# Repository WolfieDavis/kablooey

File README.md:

# kablooey

arduino based jumbo i spy game with visual interface using processing

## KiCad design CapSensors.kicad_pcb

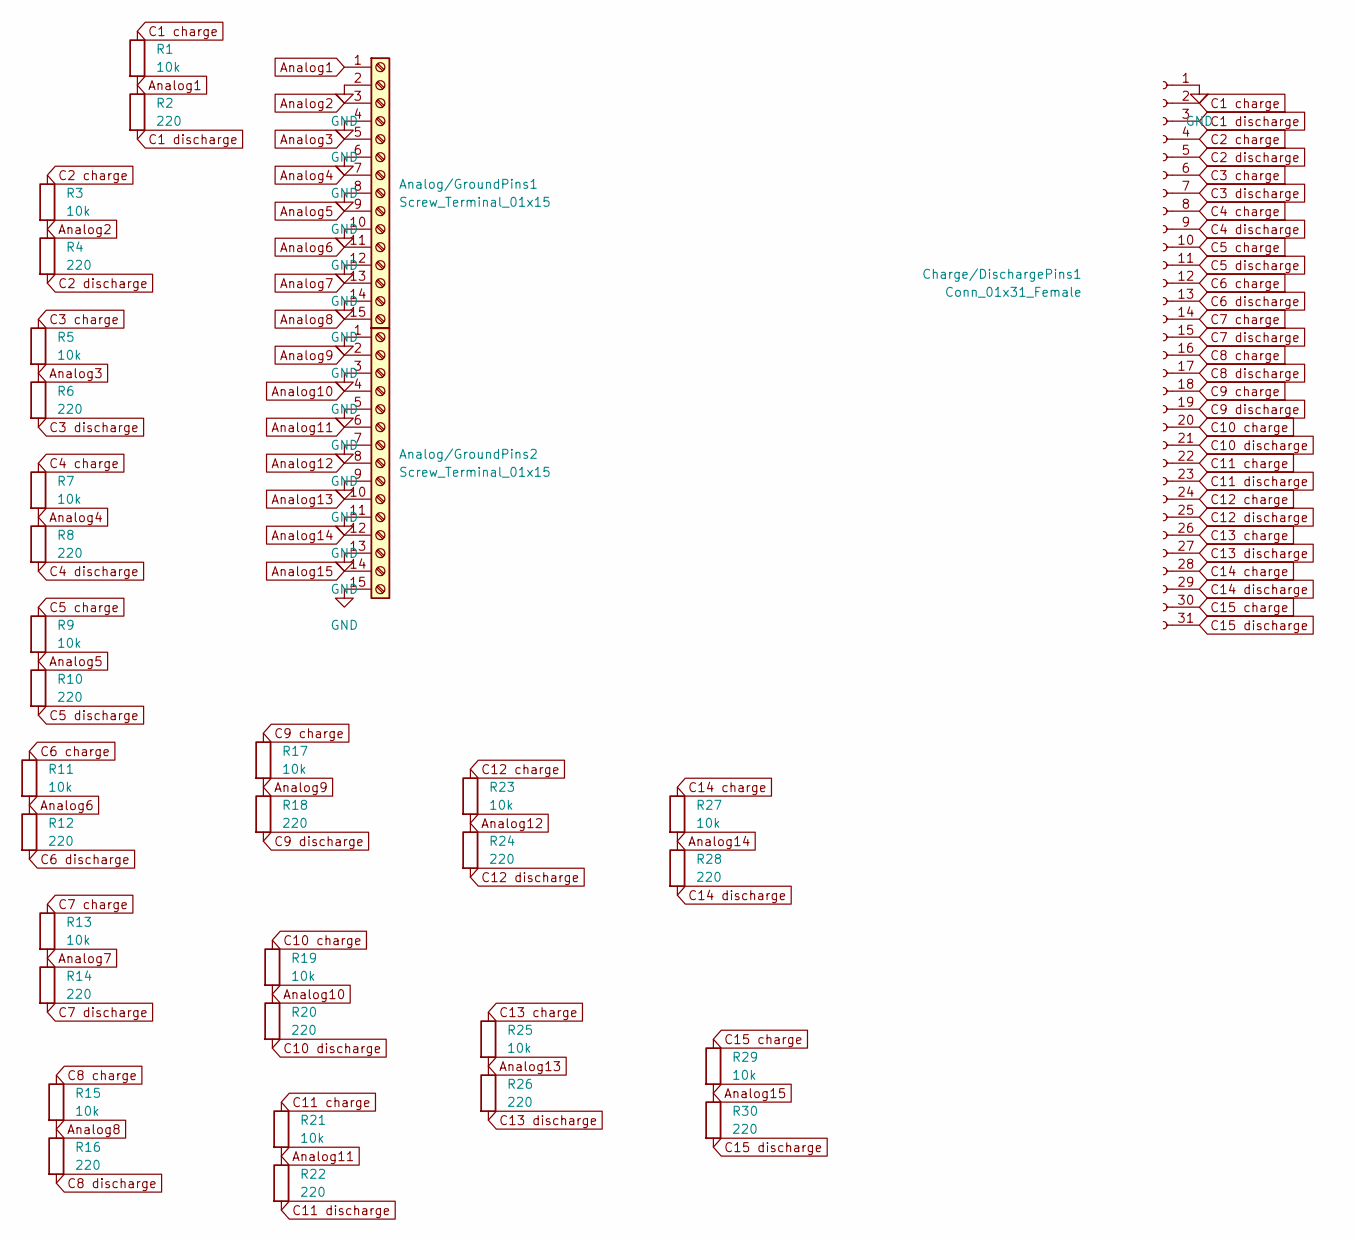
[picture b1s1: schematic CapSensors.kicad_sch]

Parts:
Analog/GroundPins1, Analog/GroundPins2: Screw_Terminal_01x15; PinHeader_1x15_P2.54mm_Vertical
Charge/DischargePins1: Conn_01x31_Female; PinHeader_1x31_P2.54mm_Vertical
R1, R3, R5, R7, R9, R11, R13, R15, R17, R19, R21, R23, R25, R27, R29: 10k; R_0603_1608Metric
R2, R4, R6, R8, R10, R12, R14, R16, R18, R20, R22, R24, R26, R28, R30: 220; R_0603_1608Metric

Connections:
Analog1: Analog/GroundPins1.1, R1.2, R2.1; also elsewhere on the board
Analog2: Analog/GroundPins1.3, R3.2, R4.1; also elsewhere on the board
Analog3: Analog/GroundPins1.5, R5.2, R6.1; also elsewhere on the board
Analog4: Analog/GroundPins1.7, R7.2, R8.1; also elsewhere on the board
Analog5: Analog/GroundPins1.9, R9.2, R10.1; also elsewhere on the board
Analog6: Analog/GroundPins1.11, R11.2, R12.1; also elsewhere on the board
Analog7: Analog/GroundPins1.13, R13.2, R14.1; also elsewhere on the board
Analog8: Analog/GroundPins1.15, R15.2, R16.1; also elsewhere on the board
Analog9: Analog/GroundPins2.2, R17.2, R18.1; also elsewhere on the board
Analog10: Analog/GroundPins2.4, R19.2, R20.1; also elsewhere on the board
Analog11: Analog/GroundPins2.6, R21.2, R22.1; also elsewhere on the board
Analog12: Analog/GroundPins2.8, R23.2, R24.1; also elsewhere on the board
Analog13: Analog/GroundPins2.10, R25.2, R26.1; also elsewhere on the board
Analog14: Analog/GroundPins2.12, R27.2, R28.1; also elsewhere on the board
Analog15: Analog/GroundPins2.14, R29.2, R30.1; also elsewhere on the board
C1 charge: Charge/DischargePins1.2, R1.1
C1 discharge: Charge/DischargePins1.3, R2.2
C2 charge: Charge/DischargePins1.4, R3.1
C2 discharge: Charge/DischargePins1.5, R4.2
C3 charge: Charge/DischargePins1.6, R5.1
C3 discharge: Charge/DischargePins1.7, R6.2
C4 charge: Charge/DischargePins1.8, R7.1
C4 discharge: Charge/DischargePins1.9, R8.2
C5 charge: Charge/DischargePins1.10, R9.1
C5 discharge: Charge/DischargePins1.11, R10.2
C6 charge: Charge/DischargePins1.12, R11.1
C6 discharge: Charge/DischargePins1.13, R12.2
C7 charge: Charge/DischargePins1.14, R13.1
C7 discharge: Charge/DischargePins1.15, R14.2
C8 charge: Charge/DischargePins1.16, R15.1
C8 discharge: Charge/DischargePins1.17, R16.2
C9 charge: Charge/DischargePins1.18, R17.1
C9 discharge: Charge/DischargePins1.19, R18.2
C10 charge: Charge/DischargePins1.20, R19.1
C10 discharge: Charge/DischargePins1.21, R20.2
C11 charge: Charge/DischargePins1.22, R21.1
C11 discharge: Charge/DischargePins1.23, R22.2
C12 charge: Charge/DischargePins1.24, R23.1
C12 discharge: Charge/DischargePins1.25, R24.2
C13 charge: Charge/DischargePins1.26, R25.1
C13 discharge: Charge/DischargePins1.27, R26.2
C14 charge: Charge/DischargePins1.28, R27.1
C14 discharge: Charge/DischargePins1.29, R28.2
C15 charge: Charge/DischargePins1.30, R29.1
C15 discharge: Charge/DischargePins1.31, R30.2
GND: Analog/GroundPins1.2, Analog/GroundPins1.4, Analog/GroundPins1.6, Analog/GroundPins1.8, Analog/GroundPins1.10, Analog/GroundPins1.12, Analog/GroundPins1.14, Analog/GroundPins2.1, Analog/GroundPins2.3, Analog/GroundPins2.5, Analog/GroundPins2.7, Analog/GroundPins2.9, Analog/GroundPins2.11, Analog/GroundPins2.13, Analog/GroundPins2.15, Charge/DischargePins1.1

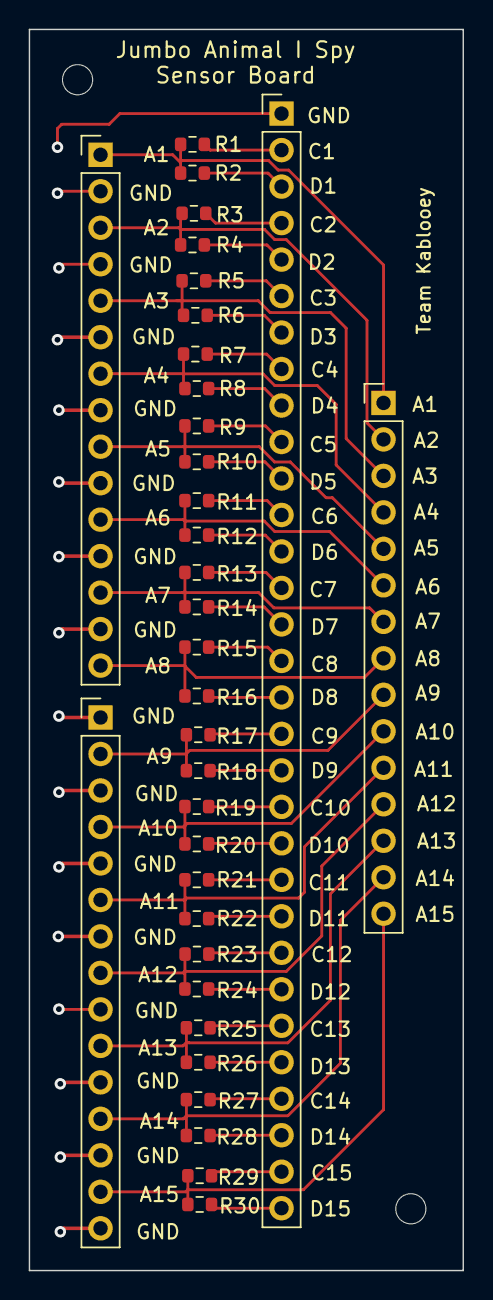
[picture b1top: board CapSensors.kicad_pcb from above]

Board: 2 copper layers, 30.2 x 86.4 mm, 34 parts (0 on the bottom side), 46 nets.

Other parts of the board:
Analogs1: Conn_01x15_Female; PinHeader_1x15_P2.54mm_Vertical

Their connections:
Analog1: Analogs1.1; also elsewhere on the board
Analog2: Analogs1.2; also elsewhere on the board
Analog3: Analogs1.3; also elsewhere on the board
Analog4: Analogs1.4; also elsewhere on the board
Analog5: Analogs1.5; also elsewhere on the board
Analog6: Analogs1.6; also elsewhere on the board
Analog7: Analogs1.7; also elsewhere on the board
Analog8: Analogs1.8; also elsewhere on the board
Analog9: Analogs1.9; also elsewhere on the board
Analog10: Analogs1.10; also elsewhere on the board
Analog11: Analogs1.11; also elsewhere on the board
Analog12: Analogs1.12; also elsewhere on the board
Analog13: Analogs1.13; also elsewhere on the board
Analog14: Analogs1.14; also elsewhere on the board
Analog15: Analogs1.15; also elsewhere on the board

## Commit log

2023-02-05 initial files
2023-02-05 cleaned up files
2023-02-05 increment through clues for now, random didn't work
2023-02-17 Add files via upload
    when you step on the sensor, the capacitance about doubles. however, sometimes the starting value is different (starts at 5k pF and doubles to 10k, other times starts at 10k and doubles to 20k) why i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
2023-02-18 intial multiple level selection implementation
2023-02-18 cleaned up clues screen for use with clue level select, working better now
2023-02-23 added countdown timer, still has testing code commented out at the bottom
2023-02-23 removed testing code and added progress bar
2023-02-24 last commit before adding hardware based control
2023-02-24 working initial hardware control
2023-02-24 hardware button control bug fixes so only prints out one number (the index of the switch) each time it is pressed
2023-02-25 Add files via upload
    most recent
2023-02-25 Add files via upload
    the actual most recent
2023-02-26 added timer to clues, and seperate page that shows the user's score after the clues and before the lederboard
2023-03-01 scores now are added to leaderboard in the correct position
2023-03-01 redid colors of level select, added leaderboard position to score screen, and added level diffuculty display to leaderboard and leaderboard works
2023-03-23 bigger text and redesign of level select and countdown, working on leaderboard, score display and clues
2023-03-31 bigger sizes more progress, checks for correct buttons, before redoing images page
2023-04-03 inital functional tested code - added board controls, redid clue screens, working on text and audio
2023-04-03 added animals to level select, fixed text by importing pngs of the text
2023-04-03 added sounds
2023-04-03 commented back in all the audio names-prev wasn't working
2023-04-07 last push before adding back in name editing - also working code from the demo
2023-04-11 fixed leaderboard ranking issue - commeted and organized saveScore too
2023-04-12 randomized clues
2023-04-12 randomized names too
2023-04-12 leaderboard input and output to files works
2023-04-12 better random name generation and leaderboard tweaks
2023-04-12 green for most recent name on leaderboard, can only edit most recent name, edit by enter key
2023-04-14 updated images to clear rounded png, normalized audio, added backup sounds if 5 7 8 too scary, redid clue screen wider and in terms of progress bar
2023-04-14 added ability to cancel score partway through, other small things - going to add easy sound mode now
2023-04-14 easy mode audio - non scary sounds, but its iffy, commenting back out for now
2023-04-15 leaderbaord edit wondow is bigger and character max for names so they don't collide with score type
2023-04-15 last commit before museum - fixed file issues, moved leaderboard column, finialized icons
